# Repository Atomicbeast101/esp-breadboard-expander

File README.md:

# ESP Breadboard Expander

Kicad-designed ESP32/ESP8266/ESP-01S breadboard expander PCB with built-in external power supply. This is to provide the option for connecting these ESP chips to the standard breadboards with a separate power supply to provide enough current for prototyping. This DC power supply also powers the ESP chip too.

This PCB was designed as my first project to understand the whole designing process as well as the JLCPCB ordering part. It has gone through 2 revisions to get it working properly.

## Specifications

* It uses a 5V DC (5.5 x 2.5mm) power supply to power the board, can use an AC to DC power supply or USB to DC jack cable to power this PCB board.
* Uses a specific ESP32 chip (ESP-WROOM-32; [Amazon Link](https://www.amazon.com/gp/product/B0B764YL3J)) to fit on this board. Other variations would most likely not fit the ESP32 slot.

## Schematic

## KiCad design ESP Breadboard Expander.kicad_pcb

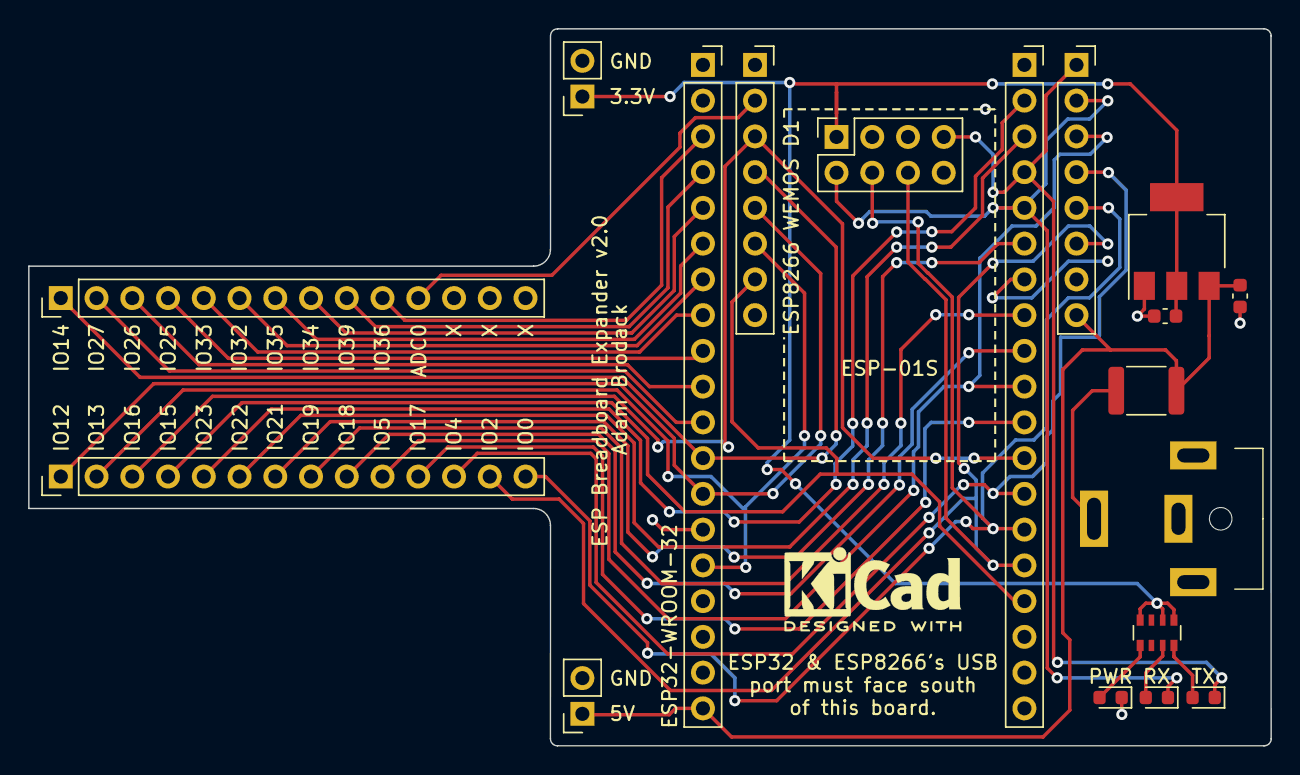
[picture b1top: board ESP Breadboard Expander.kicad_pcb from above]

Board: 4 copper layers, 88.3 x 50.9 mm, 18 parts (0 on the bottom side), 34 nets.

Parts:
C1, C2: 10uF; C_0603_1608Metric
D1: Red; LED_0603_1608Metric
D2: Green; LED_0603_1608Metric
D3: Yellow; LED_0603_1608Metric
F1: Polyfuse 30V 1A; Fuse_1812_4532Metric
J1: Conn_02x04_Odd_Even; PinSocket_2x04_P2.54mm_Vertical
J2, J3: Conn_01x08_Socket; PinSocket_1x08_P2.54mm_Vertical
J4, J5: Conn_01x19_Socket; PinSocket_1x19_P2.54mm_Vertical
J6, J7: Conn_01x14_Pin; PinHeader_1x14_P2.54mm_Vertical_UpSideDown
J8, J9: Conn_01x02_Socket; PinSocket_1x02_P2.54mm_Vertical
J10: PJ-063BH; DC_Power_Jack_PJ-063BH
RN1: 1K (4x); R_Array_Convex_4x0603
U1: AMS1117-3.3; SOT-223-3_TabPin2

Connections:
+3.3V: C2.1, J1.1, J9.1, RN1.5 (R4.2), RN1.6 (R3.2), RN1.8 (R1.2), U1.2 (VO)
+5V: C1.1, F1.2, J3.8, J4.19, J8.1, U1.3 (VI)
/ADC0: J2.2, J7.11
/IO0: J1.4, J3.5, J5.14, J6.14
/IO2: J1.6, J3.6, J5.15, J6.13
/IO4: J3.4, J5.13, J6.12
/IO5: J3.3, J5.10, J6.10
/IO12: J2.5, J4.13, J6.1
/IO13: J2.6, J4.15, J6.2
/IO14: J2.4, J4.12, J7.1
/IO15: J2.7, J5.16, J6.4
/IO16: J2.3, J5.12, J6.3
/IO17: J5.11, J6.11
/IO18: J5.9, J6.9
/IO19: J5.8, J6.8
/IO21: J5.6, J6.7
/IO22: J5.3, J6.6
/IO23: J5.2, J6.5
/IO25: J4.9, J7.4
/IO26: J4.10, J7.3
/IO27: J4.11, J7.2
/IO32: J4.7, J7.6
/IO33: J4.8, J7.5
/IO34: J4.5, J7.8
/IO35: J4.6, J7.7
/IO36: J4.3, J7.10
/IO39: J4.4, J7.9
/RX: D2.1 (K), J1.2, J3.2, J5.5
/TX: D3.1 (K), J1.7, J3.1, J5.4
GND: C1.2, C2.2, D1.1 (K), J1.8, J3.7, J4.14, J5.1, J5.7, J8.2, J9.2, J10.2, U1.1 (GND)
unnamed: D1.2 (A), RN1.1 (R1.1)
unnamed: D2.2 (A), RN1.3 (R3.1)
unnamed: D3.2 (A), RN1.4 (R4.1)
unnamed: F1.1, J10.1

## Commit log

2023-12-25 Fixed position of labels
2023-12-26 Removed diode for 3.3V power from ESP to breadboard
2023-12-26 Improved GND traces
2023-12-27 Added more labeling & checked some JLCPCB capabilities
2023-12-27 Fixed all errors found by DRC
2023-12-28 Fixed a number of issues to work with JLCPCB
2024-01-05 Fixed LED circuit & position of them
2024-01-05 Updated JLCPCB Files
2024-01-05 Fixed position of order #
2024-04-27 Updated file
2024-08-25 Added README details
2024-08-25 Added a comment for why it was designed
2024-08-25 Removed jlcpcb/ folder
2024-08-28 Updated schematic to look nicer
